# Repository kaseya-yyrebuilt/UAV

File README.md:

# UAV
Water quality sampling UAV prototype

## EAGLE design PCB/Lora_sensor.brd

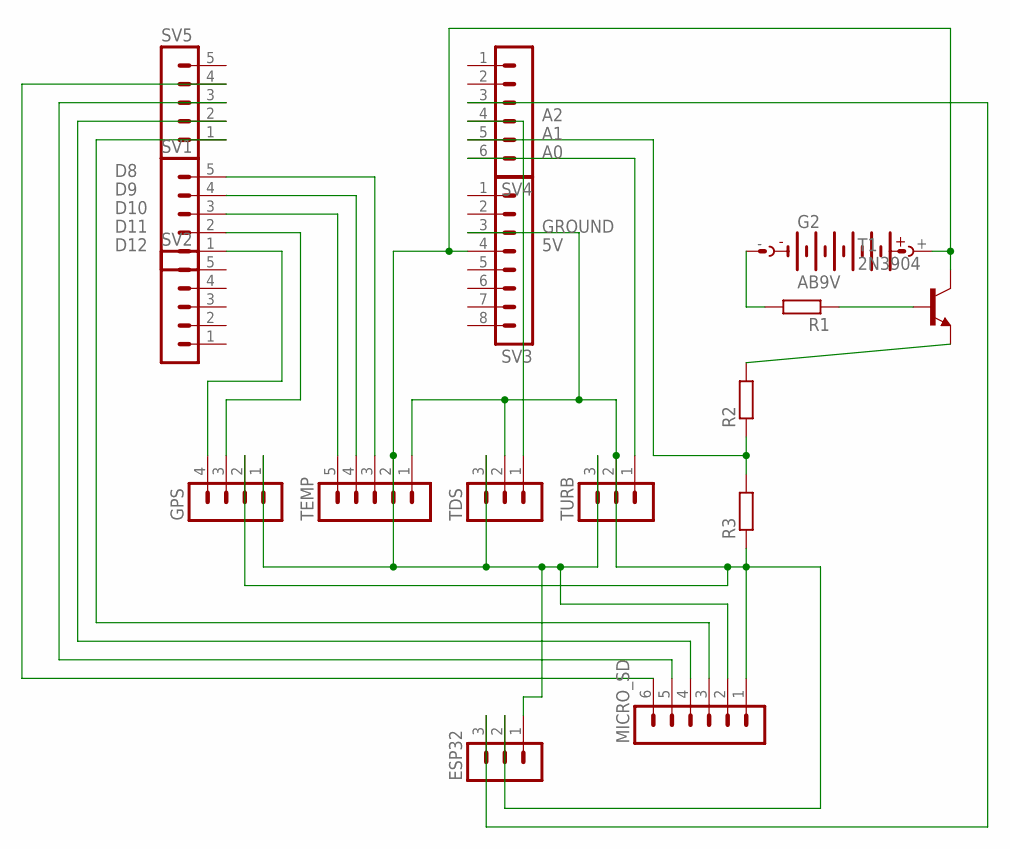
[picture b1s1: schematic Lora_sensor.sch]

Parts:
ESP32: MA03-1
G2: AB9V
GPS: MA04-1
MICRO_SD: MA06-1
R1, R2, R3: R-EU_0204/7; 0204/7
SV1, SV2, SV5: MA05-1
SV3: MA08-1
SV4: MA06-1
T1: 2N3904; TO92
TDS: MA03-1
TEMP: MA05-1
TURB: MA03-1

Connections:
5V: ESP32.1, G2.+, GPS.1, MICRO_SD.2, SV3.4, T1.1 (C), TDS.3, TEMP.2, TURB.3
A0: SV4.6, TURB.1
A1: R2.1, R3.2, SV4.5
A2: SV4.4, TDS.1
D8: SV1.5, TEMP.3
D9: SV1.4, TEMP.4
D10: SV1.3, TEMP.5
D11: GPS.3, SV1.2
D12: GPS.4, SV1.1
GROUND: ESP32.2, GPS.2, MICRO_SD.1, R3.1, SV3.3, TDS.2, TEMP.1, TURB.2
unnamed: MICRO_SD.3, SV5.1
unnamed: MICRO_SD.4, SV5.2
unnamed: MICRO_SD.5, SV5.3
unnamed: MICRO_SD.6, SV5.4
unnamed: ESP32.3, SV4.3
unnamed: R2.2, T1.3 (E)
unnamed: G2.-, R1.2
unnamed: R1.1, T1.2 (B)

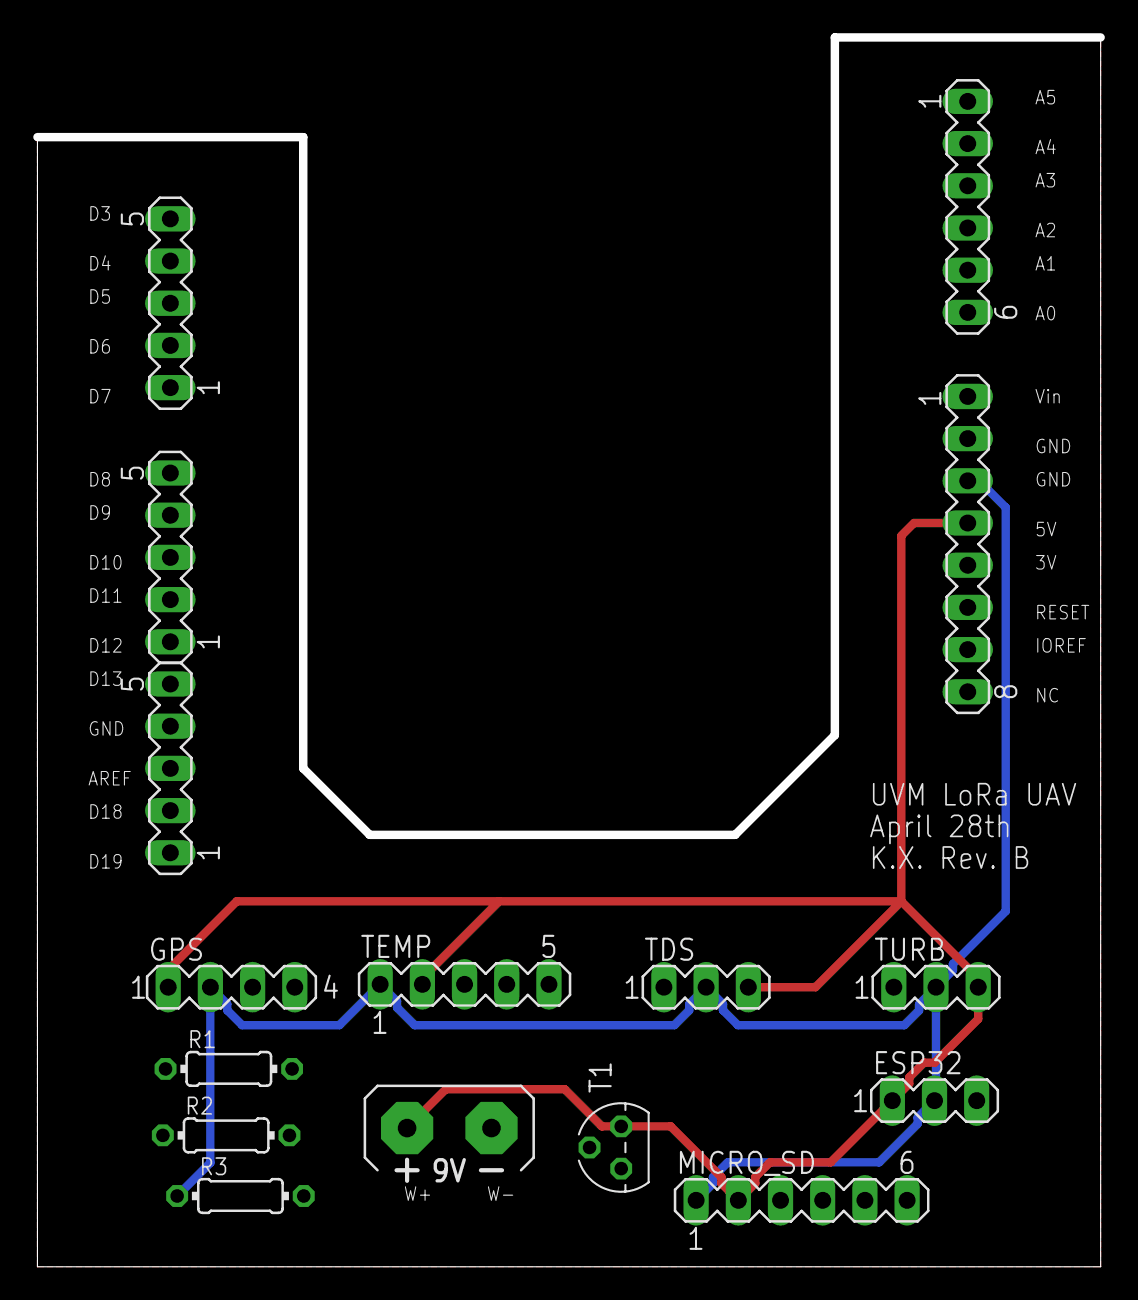
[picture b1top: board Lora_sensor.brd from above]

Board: 4 copper layers, 64.0 x 73.7 mm, 16 parts (0 on the bottom side), 18 nets.

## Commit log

2022-10-26 add code
